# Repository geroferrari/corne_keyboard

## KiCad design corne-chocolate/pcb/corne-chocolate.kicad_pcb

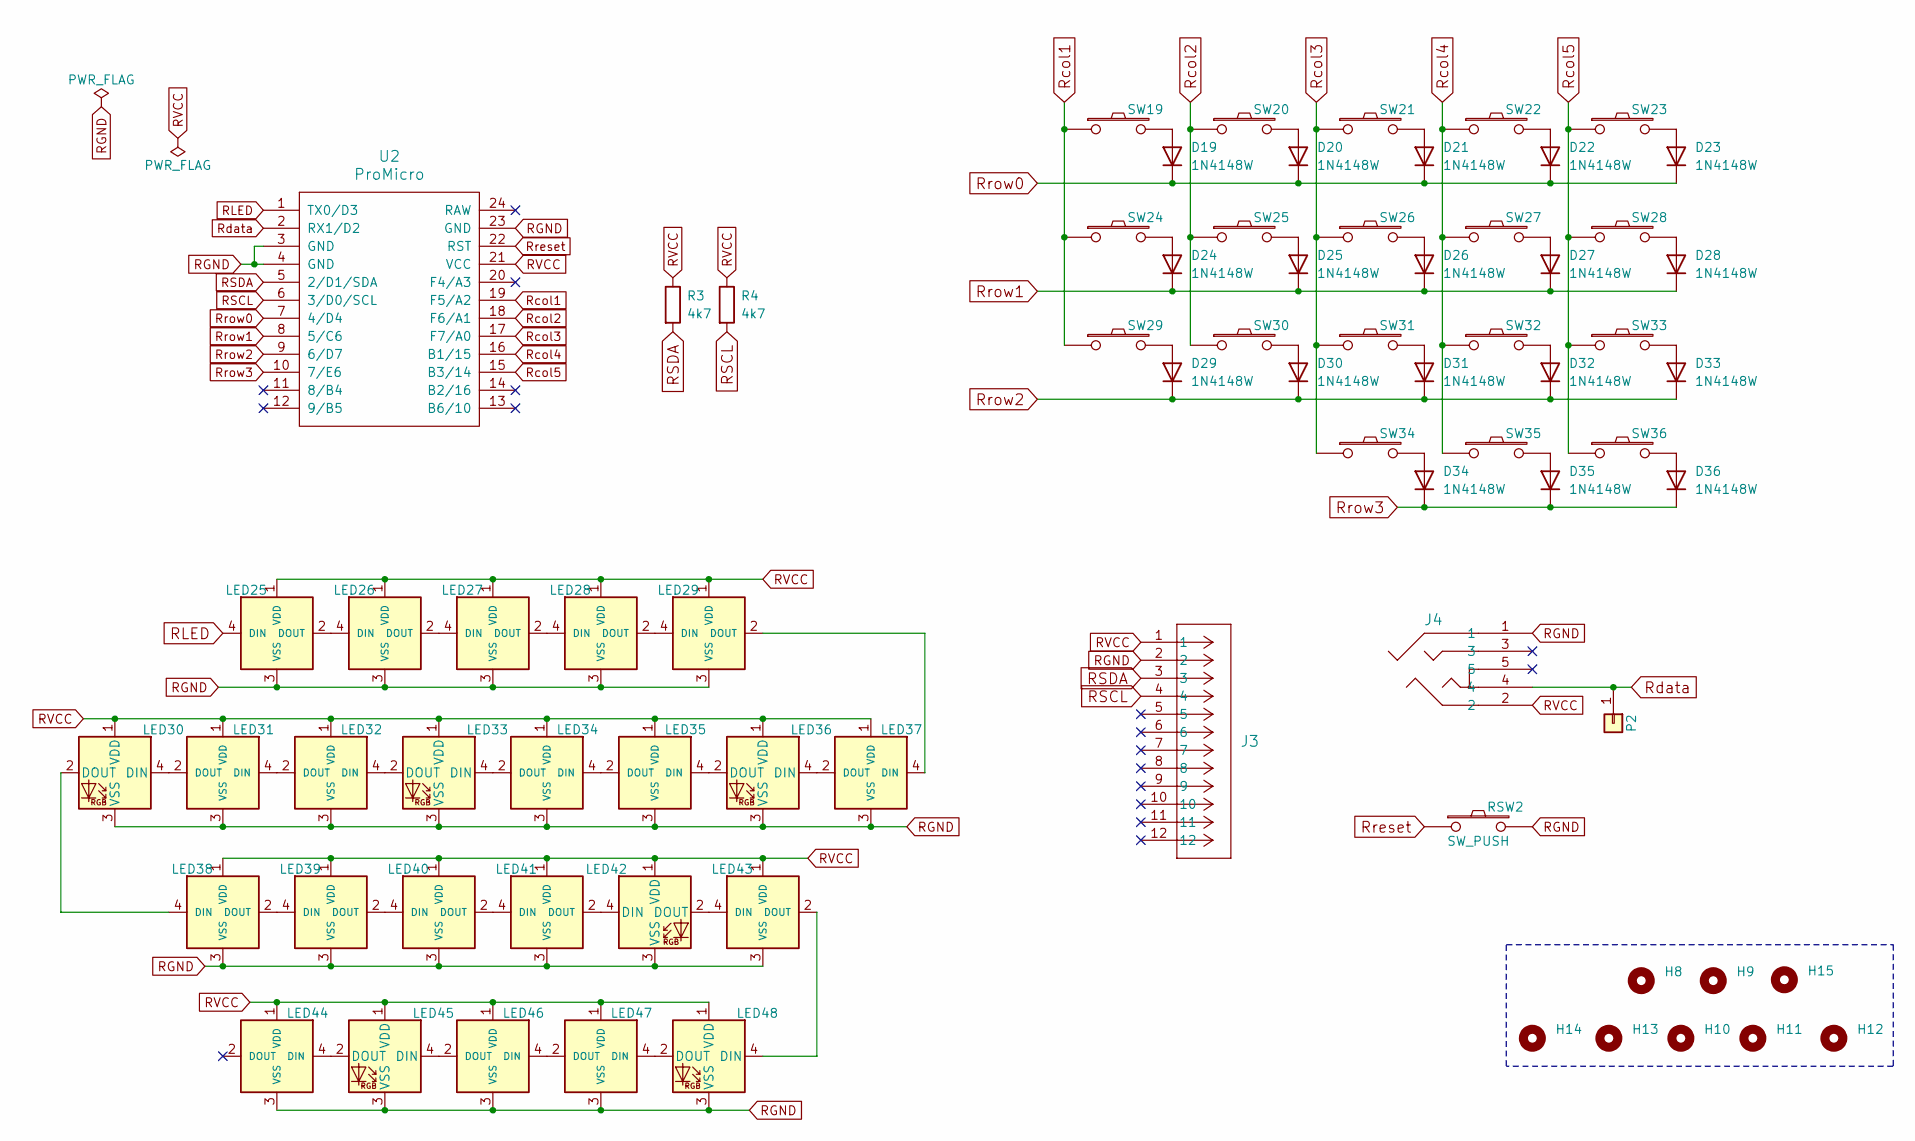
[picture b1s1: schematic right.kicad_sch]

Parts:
D19, D20, D21, D22, D23, D24, D25, D26, D27, D28, D29, D30, D31, D32, D33, D34, D35, D36: 1N4148W; D_SOD-123
H8, H9, H10, H11, H12, H13, H14, H15: MountingHole; MountingHole_2.2mm_M2_ISO14580
J3: 781271220; CON_781271220
J4: 54-00174; 54-00174_TEN
LED25, LED26, LED27, LED28, LED29, LED31, LED32, LED34, LED35, LED37, LED38, LED39, LED40, LED41, LED43, LED44, LED46, LED47: YS-SK6812MINI-E; LED_SK6812-MINI-E
LED30, LED33, LED36, LED42, LED45, LED48: WS2812B; LED_WS2812B_PLCC4_5.0x5.0mm_P3.2mm
P2: Conn_01x01; 1pin_conn
R3, R4: 4k7; R_0805_2012Metric_Pad1.20x1.40mm_HandSolder
RSW2: SW_PUSH; ResetSW_1side
SW19, SW20, SW21, SW22, SW23, SW24, SW25, SW26, SW27, SW28, SW29, SW30, SW31, SW32, SW33, SW34, SW35: SW_PUSH; ChocV1_V2_Hotswap
SW36: SW_PUSH; ChocV1_V2_Hotswap_1.5u
U2: ProMicro; ProMicro_v2_1side

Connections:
unnamed: D19.2 (A), SW19.2
unnamed: D20.2 (A), SW20.2
unnamed: D21.2 (A), SW21.2
unnamed: D22.2 (A), SW22.2
unnamed: D23.2 (A), SW23.2
unnamed: D24.2 (A), SW24.2
unnamed: D25.2 (A), SW25.2
unnamed: D26.2 (A), SW26.2
unnamed: D27.2 (A), SW27.2
unnamed: D28.2 (A), SW28.2
unnamed: D29.2 (A), SW29.2
unnamed: D30.2 (A), SW30.2
unnamed: D31.2 (A), SW31.2
unnamed: D32.2 (A), SW32.2
unnamed: D33.2 (A), SW33.2
unnamed: D34.2 (A), SW34.2
unnamed: D35.2 (A), SW35.2
unnamed: D36.2 (A), SW36.2
unnamed: LED25.2 (DOUT), LED26.4 (DIN)
unnamed: LED26.2 (DOUT), LED27.4 (DIN)
unnamed: LED27.2 (DOUT), LED28.4 (DIN)
unnamed: LED28.2 (DOUT), LED29.4 (DIN)
unnamed: LED29.2 (DOUT), LED37.4 (DIN)
unnamed: LED30.4 (DIN), LED31.2 (DOUT)
unnamed: LED30.2 (DOUT), LED38.4 (DIN)
unnamed: LED31.4 (DIN), LED32.2 (DOUT)
unnamed: LED32.4 (DIN), LED33.2 (DOUT)
unnamed: LED33.4 (DIN), LED34.2 (DOUT)
unnamed: LED34.4 (DIN), LED35.2 (DOUT)
unnamed: LED35.4 (DIN), LED36.2 (DOUT)
unnamed: LED36.4 (DIN), LED37.2 (DOUT)
unnamed: LED38.2 (DOUT), LED39.4 (DIN)
unnamed: LED39.2 (DOUT), LED40.4 (DIN)
unnamed: LED40.2 (DOUT), LED41.4 (DIN)
unnamed: LED41.2 (DOUT), LED42.4 (DIN)
unnamed: LED42.2 (DOUT), LED43.4 (DIN)
unnamed: LED43.2 (DOUT), LED48.4 (DIN)
unnamed: LED44.4 (DIN), LED45.2 (DOUT)
unnamed: LED45.4 (DIN), LED46.2 (DOUT)
unnamed: LED46.4 (DIN), LED47.2 (DOUT)
unnamed: LED47.4 (DIN), LED48.2 (DOUT)
RGND: J3.2, J4.1, LED25.3 (VSS), LED26.3 (VSS), LED27.3 (VSS), LED28.3 (VSS), LED29.3 (VSS), LED30.3 (VSS), LED31.3 (VSS), LED32.3 (VSS), LED33.3 (VSS), LED34.3 (VSS), LED35.3 (VSS), LED36.3 (VSS), LED37.3 (VSS), LED38.3 (VSS), LED39.3 (VSS), LED40.3 (VSS), LED41.3 (VSS), LED42.3 (VSS), LED43.3 (VSS), LED44.3 (VSS), LED45.3 (VSS), LED46.3 (VSS), LED47.3 (VSS), LED48.3 (VSS), RSW2.2, U2.3 (GND), U2.4 (GND), U2.23 (GND)
RLED: LED25.4 (DIN), U2.1 (TX0/D3)
RSCL: J3.4, R4.2, U2.6 (3/D0/SCL)
RSDA: J3.3, R3.2, U2.5 (2/D1/SDA)
RVCC: J3.1, J4.2, LED25.1 (VDD), LED26.1 (VDD), LED27.1 (VDD), LED28.1 (VDD), LED29.1 (VDD), LED30.1 (VDD), LED31.1 (VDD), LED32.1 (VDD), LED33.1 (VDD), LED34.1 (VDD), LED35.1 (VDD), LED36.1 (VDD), LED37.1 (VDD), LED38.1 (VDD), LED39.1 (VDD), LED40.1 (VDD), LED41.1 (VDD), LED42.1 (VDD), LED43.1 (VDD), LED44.1 (VDD), LED45.1 (VDD), LED46.1 (VDD), LED47.1 (VDD), LED48.1 (VDD), R3.1, R4.1, U2.21 (VCC)
Rcol1: SW19.1, SW24.1, SW29.1, U2.19 (F5/A2)
Rcol2: SW20.1, SW25.1, SW30.1, U2.18 (F6/A1)
Rcol3: SW21.1, SW26.1, SW31.1, SW34.1, U2.17 (F7/A0)
Rcol4: SW22.1, SW27.1, SW32.1, SW35.1, U2.16 (B1/15)
Rcol5: SW23.1, SW28.1, SW33.1, SW36.1, U2.15 (B3/14)
Rdata: J4.4, P2.1, U2.2 (RX1/D2)
Rreset: RSW2.1, U2.22 (RST)
Rrow0: D19.1 (K), D20.1 (K), D21.1 (K), D22.1 (K), D23.1 (K), U2.7 (4/D4)
Rrow1: D24.1 (K), D25.1 (K), D26.1 (K), D27.1 (K), D28.1 (K), U2.8 (5/C6)
Rrow2: D29.1 (K), D30.1 (K), D31.1 (K), D32.1 (K), D33.1 (K), U2.9 (6/D7)
Rrow3: D34.1 (K), D35.1 (K), D36.1 (K), U2.10 (7/E6)

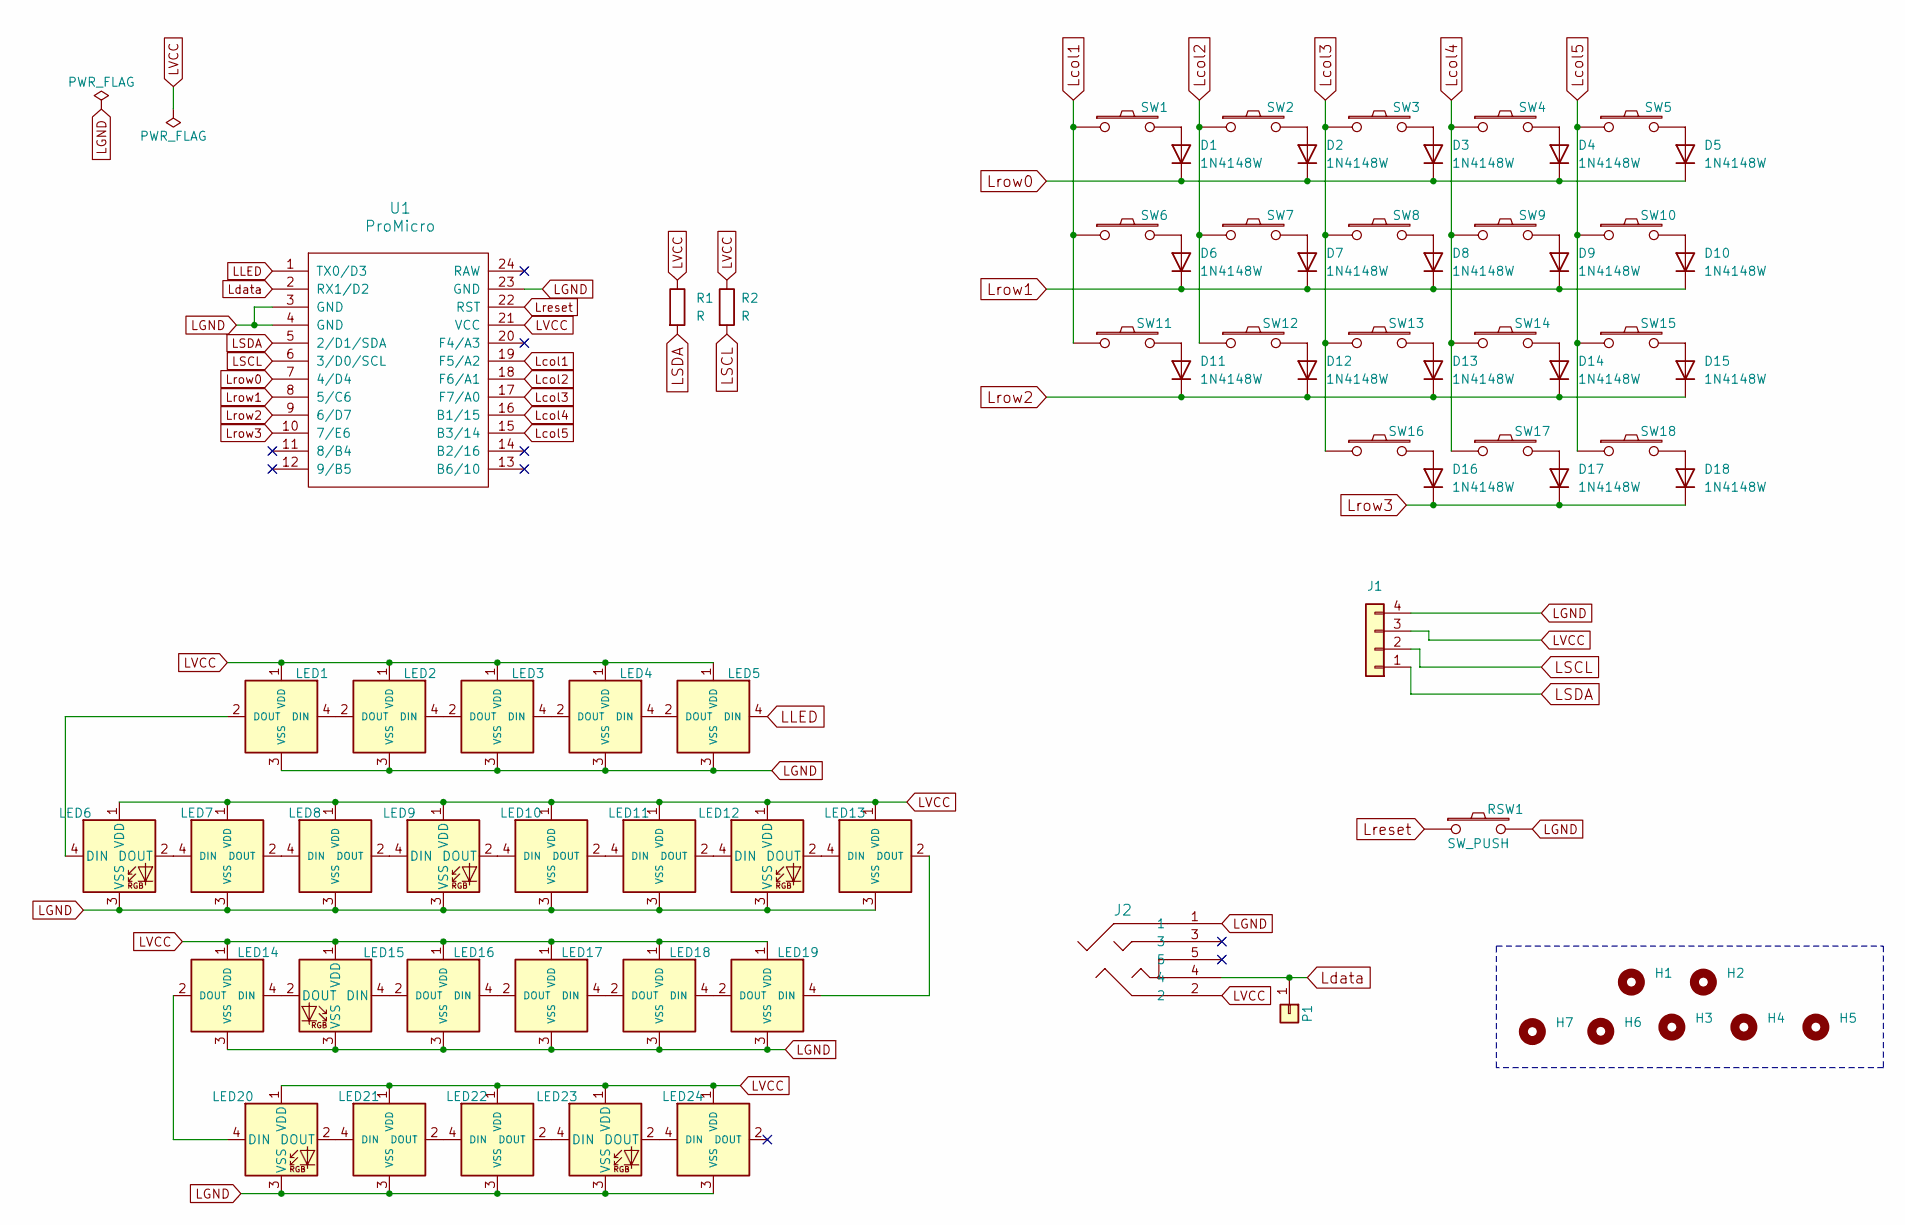
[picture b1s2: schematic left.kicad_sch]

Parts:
D1, D2, D3, D4, D5, D6, D7, D8, D9, D10, D11, D12, D13, D14, D15, D16, D17, D18: 1N4148W; D_SOD-123
H1, H2, H3, H4, H5, H6, H7: MountingHole; MountingHole_2.2mm_M2_ISO14580
J1: Conn_01x04; OLED_1side
J2: 54-00174; 54-00174_TEN
LED1, LED2, LED3, LED4, LED5, LED7, LED8, LED10, LED11, LED13, LED14, LED16, LED17, LED18, LED19, LED21, LED22, LED24: YS-SK6812MINI-E; LED_SK6812-MINI-E
LED6, LED9, LED12, LED15, LED20, LED23: WS2812B; LED_WS2812B_PLCC4_5.0x5.0mm_P3.2mm
P1: Conn_01x01; 1pin_conn
R1, R2: R; R_0805_2012Metric_Pad1.20x1.40mm_HandSolder
RSW1: SW_PUSH; ResetSW_1side
SW1, SW2, SW3, SW4, SW5, SW6, SW7, SW8, SW9, SW10, SW11, SW12, SW13, SW14, SW15, SW16, SW17: SW_PUSH; ChocV1_V2_Hotswap
SW18: SW_PUSH; ChocV1_V2_Hotswap_1.5u
U1: ProMicro; ProMicro_v2_1side

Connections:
LGND: J1.4, J2.1, LED1.3 (VSS), LED2.3 (VSS), LED3.3 (VSS), LED4.3 (VSS), LED5.3 (VSS), LED6.3 (VSS), LED7.3 (VSS), LED8.3 (VSS), LED9.3 (VSS), LED10.3 (VSS), LED11.3 (VSS), LED12.3 (VSS), LED13.3 (VSS), LED14.3 (VSS), LED15.3 (VSS), LED16.3 (VSS), LED17.3 (VSS), LED18.3 (VSS), LED19.3 (VSS), LED20.3 (VSS), LED21.3 (VSS), LED22.3 (VSS), LED23.3 (VSS), LED24.3 (VSS), RSW1.2, U1.3 (GND), U1.4 (GND), U1.23 (GND)
LLED: LED5.4 (DIN), U1.1 (TX0/D3)
LSCL: J1.2, R2.2, U1.6 (3/D0/SCL)
LSDA: J1.1, R1.2, U1.5 (2/D1/SDA)
LVCC: J1.3, J2.2, LED1.1 (VDD), LED2.1 (VDD), LED3.1 (VDD), LED4.1 (VDD), LED5.1 (VDD), LED6.1 (VDD), LED7.1 (VDD), LED8.1 (VDD), LED9.1 (VDD), LED10.1 (VDD), LED11.1 (VDD), LED12.1 (VDD), LED13.1 (VDD), LED14.1 (VDD), LED15.1 (VDD), LED16.1 (VDD), LED17.1 (VDD), LED18.1 (VDD), LED19.1 (VDD), LED20.1 (VDD), LED21.1 (VDD), LED22.1 (VDD), LED23.1 (VDD), LED24.1 (VDD), R1.1, R2.1, U1.21 (VCC)
Lcol1: SW1.1, SW6.1, SW11.1, U1.19 (F5/A2)
Lcol2: SW2.1, SW7.1, SW12.1, U1.18 (F6/A1)
Lcol3: SW3.1, SW8.1, SW13.1, SW16.1, U1.17 (F7/A0)
Lcol4: SW4.1, SW9.1, SW14.1, SW17.1, U1.16 (B1/15)
Lcol5: SW5.1, SW10.1, SW15.1, SW18.1, U1.15 (B3/14)
Ldata: J2.4, P1.1, U1.2 (RX1/D2)
Lreset: RSW1.1, U1.22 (RST)
Lrow0: D1.1 (K), D2.1 (K), D3.1 (K), D4.1 (K), D5.1 (K), U1.7 (4/D4)
Lrow1: D6.1 (K), D7.1 (K), D8.1 (K), D9.1 (K), D10.1 (K), U1.8 (5/C6)
Lrow2: D11.1 (K), D12.1 (K), D13.1 (K), D14.1 (K), D15.1 (K), U1.9 (6/D7)
Lrow3: D16.1 (K), D17.1 (K), D18.1 (K), U1.10 (7/E6)
unnamed: D1.2 (A), SW1.2
unnamed: D2.2 (A), SW2.2
unnamed: D3.2 (A), SW3.2
unnamed: D4.2 (A), SW4.2
unnamed: D5.2 (A), SW5.2
unnamed: D6.2 (A), SW6.2
unnamed: D7.2 (A), SW7.2
unnamed: D8.2 (A), SW8.2
unnamed: D9.2 (A), SW9.2
unnamed: D10.2 (A), SW10.2
unnamed: D11.2 (A), SW11.2
unnamed: D12.2 (A), SW12.2
unnamed: D13.2 (A), SW13.2
unnamed: D14.2 (A), SW14.2
unnamed: D15.2 (A), SW15.2
unnamed: D16.2 (A), SW16.2
unnamed: D17.2 (A), SW17.2
unnamed: D18.2 (A), SW18.2
unnamed: LED1.4 (DIN), LED2.2 (DOUT)
unnamed: LED1.2 (DOUT), LED6.4 (DIN)
unnamed: LED2.4 (DIN), LED3.2 (DOUT)
unnamed: LED3.4 (DIN), LED4.2 (DOUT)
unnamed: LED4.4 (DIN), LED5.2 (DOUT)
unnamed: LED6.2 (DOUT), LED7.4 (DIN)
unnamed: LED7.2 (DOUT), LED8.4 (DIN)
unnamed: LED8.2 (DOUT), LED9.4 (DIN)
unnamed: LED9.2 (DOUT), LED10.4 (DIN)
unnamed: LED10.2 (DOUT), LED11.4 (DIN)
unnamed: LED11.2 (DOUT), LED12.4 (DIN)
unnamed: LED12.2 (DOUT), LED13.4 (DIN)
unnamed: LED13.2 (DOUT), LED19.4 (DIN)
unnamed: LED14.4 (DIN), LED15.2 (DOUT)
unnamed: LED14.2 (DOUT), LED20.4 (DIN)
unnamed: LED15.4 (DIN), LED16.2 (DOUT)
unnamed: LED16.4 (DIN), LED17.2 (DOUT)
unnamed: LED17.4 (DIN), LED18.2 (DOUT)
unnamed: LED18.4 (DIN), LED19.2 (DOUT)
unnamed: LED20.2 (DOUT), LED21.4 (DIN)
unnamed: LED21.2 (DOUT), LED22.4 (DIN)
unnamed: LED22.2 (DOUT), LED23.4 (DIN)
unnamed: LED23.2 (DOUT), LED24.4 (DIN)

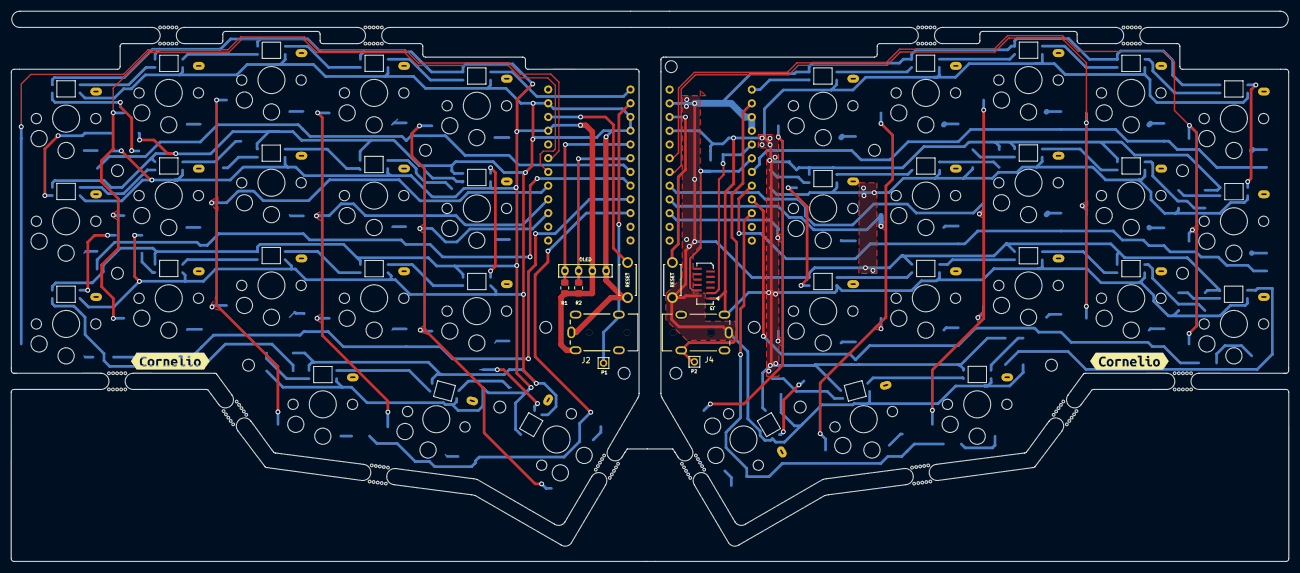
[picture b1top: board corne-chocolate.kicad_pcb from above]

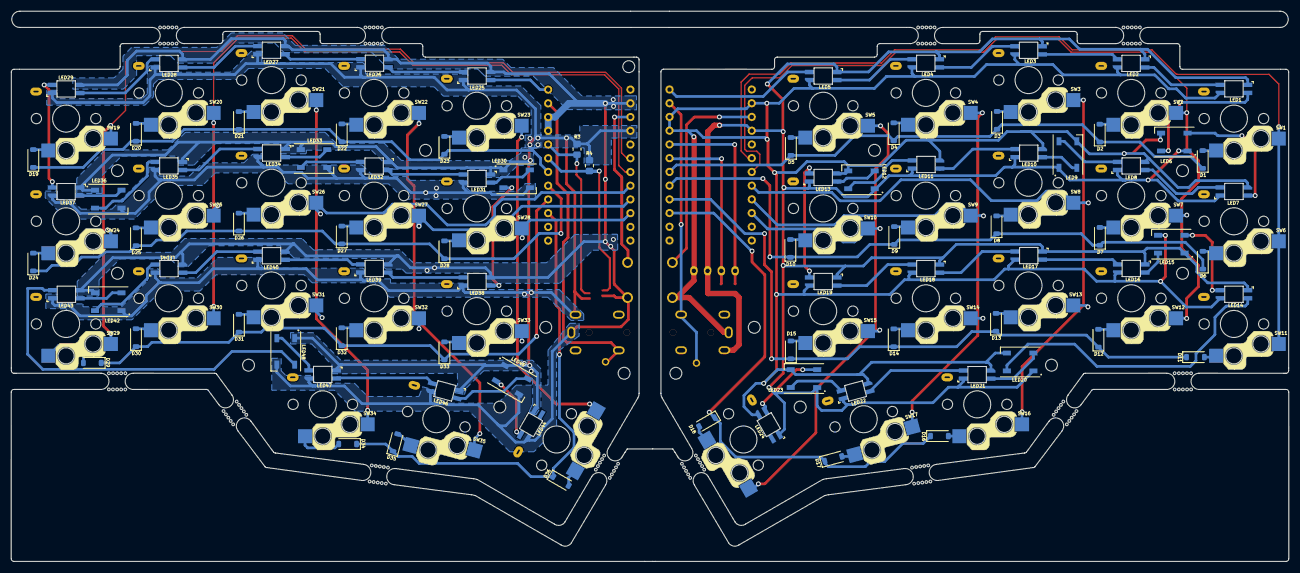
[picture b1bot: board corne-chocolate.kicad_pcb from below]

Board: 2 copper layers, 236.4 x 101.8 mm, 163 parts (92 on the bottom side), 114 nets.

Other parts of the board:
kibuzzard-65BBD98A, kibuzzard-65BBD98A#2: G***; kibuzzard-65BBD98A
mouse-bite-3mm-slot, mouse-bite-3mm-slot#2, mouse-bite-3mm-slot#3, mouse-bite-3mm-slot#4, mouse-bite-3mm-slot#5, mouse-bite-3mm-slot#6, mouse-bite-3mm-slot#7, mouse-bite-3mm-slot#8, mouse-bite-3mm-slot#9, mouse-bite-3mm-slot#10, mouse-bite-3mm-slot#11, mouse-bite-3mm-slot#12: VAL**; mouse-bite-3mm-slot

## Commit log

2024-01-30 leave only chocolate corne stuff
2024-01-31 starts non-reversable pcbs routing
2024-01-31 removes all reversible routing
2024-02-01 starts re-routing. switch to a 3x5 kbd
2024-02-01 pcb with ohspark constraints
2024-02-01 routing..
2024-02-02 more routing
2024-02-02 all items connected
2024-02-05 finishes routing
2024-02-05 updates some footprints
2024-02-05 reannotates
2024-02-05 starts component review
2024-02-08 footprint verified, list of components with their vendors sites
2024-02-09 updates part list
2024-02-09 switch to nrf52840 micro. All items from amazon
2024-02-10 adds right keyboard
2024-02-13 adds right board. stars routing
2024-02-16 several important fixes
2024-02-16 breakaway tabs
2024-02-19 zones in right keyboard
2024-02-19 zones in left keyboard
2024-03-01 update folders
2024-03-16 new board shape
2024-03-17 adds qmk config files
2024-03-17 qmk config
2024-03-21 updates config
2024-04-02 updates in casing and firmware
2024-04-06 updates casing
2024-07-19 updates board
2024-07-19 updates 3d designs
